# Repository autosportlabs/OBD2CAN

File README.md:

OBD2CAN
=======

OBD2CAN allows cars with pre-CAN OBDII enabled ECUs (1996-2007) to emulate a CAN-OBDII interface.

Target
======

OBD2CAN was originally designed as an enhancement to the RaceCapture and RaceCapture/Pro line of hardware, but could theoretically be used with any device that can only communicate with CAN-OBDII enabled ECUs.

Principal of Operation
======================

The operation of OBD2CAN is straightforward:

CAN-OBDII requests are received by OBD2CAN and are forwarded on to the legacy-OBDII interface, using
a STN1110 processor and interface circuitry. 

Legacy-OBDII PID responses are received from the STN1110, and transformed back into the equivalent CAN-OBDII response.

Firmware
========
The firmware is targeted for the STM32F072, and uses ChibiOS as a RTOS. 

Compiling
=========
Compiling requires arm-none-eabi gcc version 4.7.4 20130913

From the firmware directory issue:

> make clean

> make

Flashing
========
* ST bootloader

The firmware image can be flashed using the ST bootloader using the USART1 header after activating BOOT mode. On the OBD2CAN hardware the BOOT jumper pads is adjacent to the USART1 header. The USART header can be connected to a common FTDI 3.3v USB-USART cable (TTL-232R-3V3).

* JTAG SWD

An openocd script is provided to flash the STM32 via SWD, using a ST-LINK/V2

Operation
=========

CAN PID requests are received per OBDII SAE specifications and are translated 1:1 to STN1110 PID requests for the target ECU. 
* 500KBPS
* 11 bit

Protocol is set for automatic detection. 

Diagnostic and command/control CAN messages
===========================================

Control Message
===============
The control message allows some control over the OBD2CAN module's settings

CAN ID: 62344

* Byte 0: Sub command.
 * always 0x01

* Byte 1: Debug level on UART header
 * 0: no logging
 * 1: info level logging
 * 2: trace level logging

* Byte 2: Reset STN1110
 * 0: do not reset
 * 1: perform a hard reset

* Byte 3: Set OBDII protocol
Affects AT SP command, see ELM327 manual. If different than the current setting, triggers a reset of the STN1110
 * 0: auto detect (power up default)
 * 1: J1850 PWM
 * 2: J1850 VPW
 * 3: ISO 9141-2
 * 4: ISO 14230-4

Diagnostic
==========
The OBD2CAN will broadcast a diagnostic message at 1Hz with the following information:

CAN ID: 62345

* Byte 0: Detected protocol
 * 0: auto detect (still detecting)
 * 1: J1850 PWM
 * 2: J1850 VPW
 * 3: ISO 9141-2
 * 4: ISO 14230-4

* Byte 1: Last error code
 * 0: STN1110_ERROR_NONE,
 * 1: STN1110_ERROR_STOPPED,
 * 2: STN1110_ERROR_NO_DATA,
 * 3: STN1110_ERROR_BUS_INIT

* Byte 2-3: STN1110 request/reply latency, in ms. 
 * Little Endian

* Byte 4: reserved

* Byte 5: firmware major version

* Byte 6: firmware minor version

* Byte 7: firmware patch version

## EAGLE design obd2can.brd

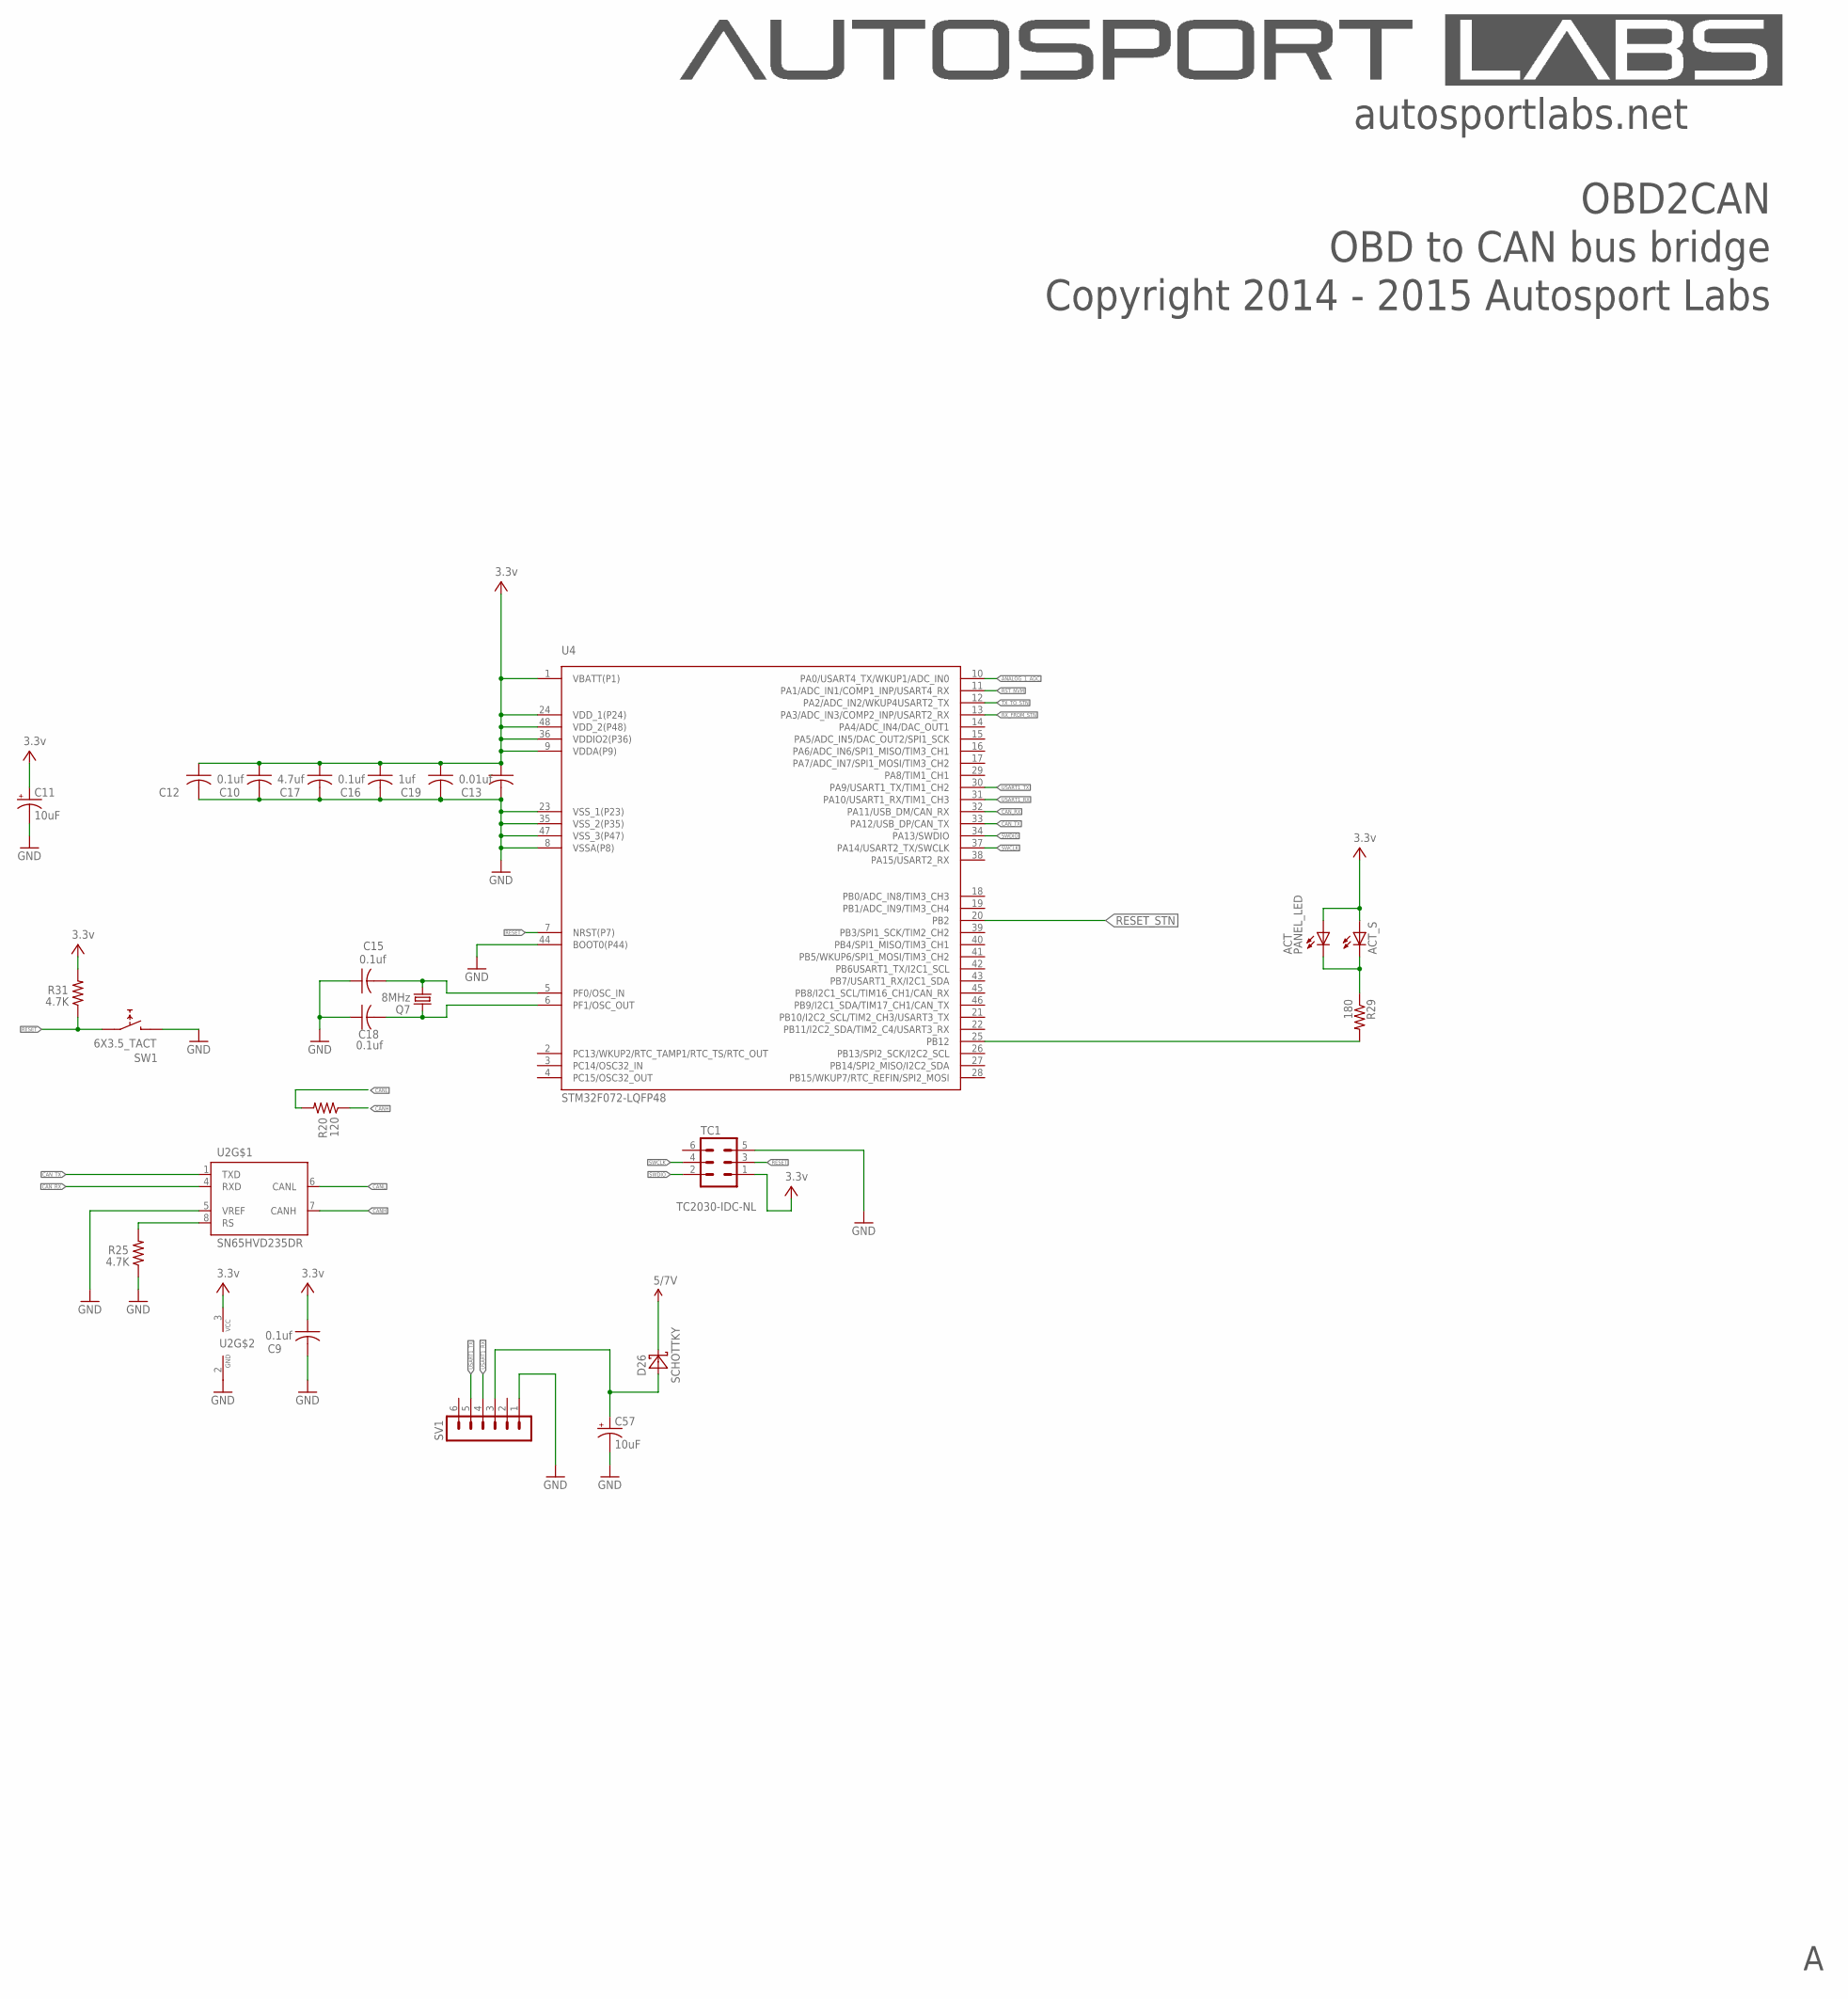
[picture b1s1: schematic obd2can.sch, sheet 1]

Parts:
ACT: PANEL_LED; RIGHTANGLE_CML_5323F5
ACT_S: LEDCHIPLED_0603; CHIPLED_0603
C9, C10, C15, C16, C18: 0.1uf; C0603K
C11, C57: 10uF; SMC_A
C12, C17: 4.7uf; C0603K
C13: 0.01uf; C0603K
C19: 1uf; C0603K
D26: SCHOTTKY; SMA
Q7: 8MHz; CRYSTAL-SMD-5X3
R20: 120; R0603
R25, R31: 4.7K; R0603
R29: 180; 0402-RES
SV1: MA06-1
SW1: 6X3.5_TACT; TACT_6X3.5
TC1: TC2030-IDC-NL
U2: SN65HVD235DR; SO08
U4: STM32F072-LQFP48; LQFP48

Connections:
ANALOG_1_ADC: U4.10 (PA0/USART4_TX/WKUP1/ADC_IN0)
CANH: R20.1, U2.7 (CANH); also elsewhere on the board
CANL: R20.2, U2.6 (CANL); also elsewhere on the board
CAN_RX: U2.4 (RXD), U4.32 (PA11/USB_DM/CAN_RX)
CAN_TX: U2.1 (TXD), U4.33 (PA12/USB_DP/CAN_TX)
GND: C9.2, C10.2, C11.-, C12.2, C13.2, C15.1, C16.2, C17.2, C18.1, C19.2, C57.-, R25.1, SV1.1, SW1.P$2 (2), TC1.5, U2.2 (GND), U2.5 (VREF), U4.8 (VSSA(P8)), U4.23 (VSS_1(P23)), U4.35 (VSS_2(P35)), U4.44 (BOOT0(P44)), U4.47 (VSS_3(P47)); also elsewhere on the board
GND1: ACT.C, ACT_S.C, R29.1
unnamed: R29.2, U4.25 (PB12)
unnamed: R25.2, U2.8 (RS)
unnamed: C18.2, Q7.3 (2), U4.6 (PF1/OSC_OUT)
unnamed: C15.2, Q7.1, U4.5 (PF0/OSC_IN)
RESET: R31.1, SW1.P$1 (1), TC1.3, U4.7 (NRST(P7))
RESET_STN: U4.20 (PB2); also elsewhere on the board
RST_NVM: U4.11 (PA1/ADC_IN1/COMP1_INP/USART4_RX); also elsewhere on the board
RX_FROM_STN: U4.13 (PA3/ADC_IN3/COMP2_INP/USART2_RX); also elsewhere on the board
SWCLK: TC1.4, U4.37 (PA14/USART2_TX/SWCLK)
SWDIO: TC1.2, U4.34 (PA13/SWDIO)
TX_TO_STN: U4.12 (PA2/ADC_IN2/WKUP4USART2_TX); also elsewhere on the board
USART1_RX: SV1.4, U4.31 (PA10/USART1_RX/TIM1_CH3)
USART1_TX: SV1.5, U4.30 (PA9/USART1_TX/TIM1_CH2)
V+: ACT.A, ACT_S.A, C9.1, C10.1, C11.+, C12.1, C13.1, C16.1, C17.1, C19.1, R31.2, TC1.1, U2.3 (VCC), U4.1 (VBATT(P1)), U4.9 (VDDA(P9)), U4.24 (VDD_1(P24)), U4.36 (VDDIO2(P36)), U4.48 (VDD_2(P48)); also elsewhere on the board
VBUS: C57.+, D26.A, SV1.3
VCC: D26.C; also elsewhere on the board

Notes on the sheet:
Copyright 2014 - 2015 Autosport Labs
OBD2CAN
autosportlabs.net
OBD to CAN bus bridge

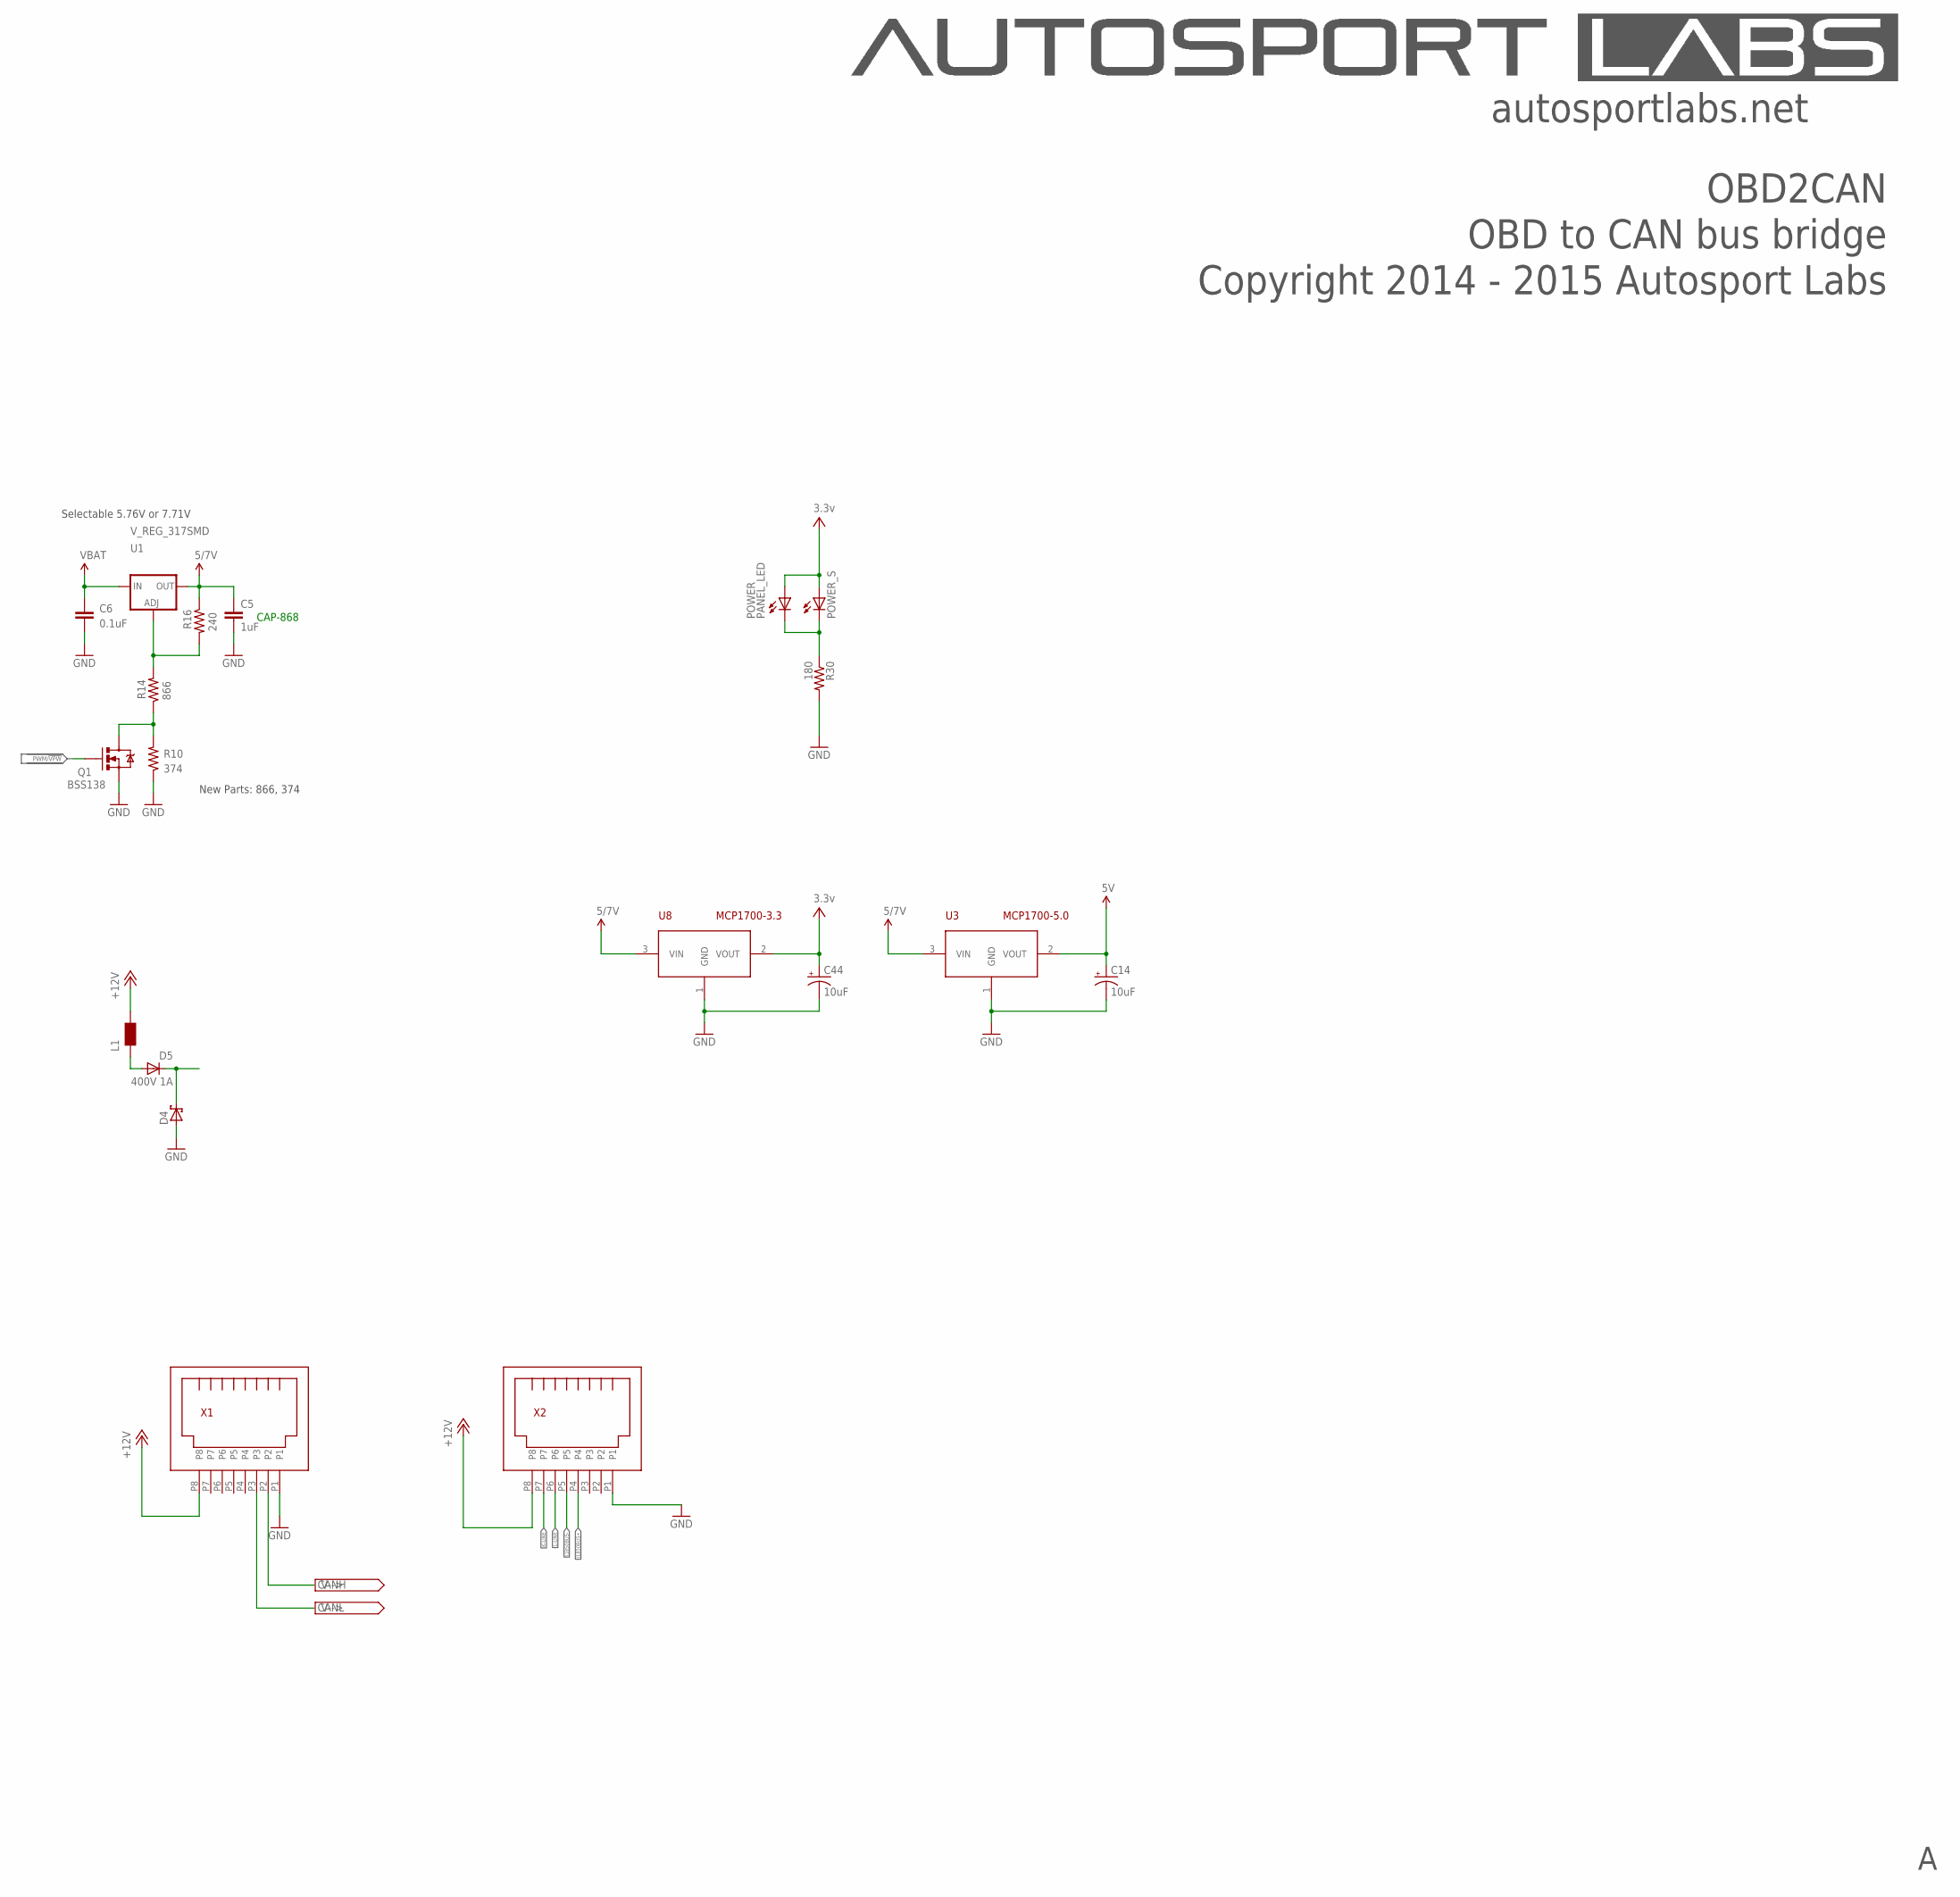
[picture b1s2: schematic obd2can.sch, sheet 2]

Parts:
C5: 1uF; 0402-CAP
C6: 0.1uF; 0402-CAP
C14, C44: 10uF; SMC_A
D4: SCHOTTKY-DIODESMC; SMC
D5: 400V 1A; SMA
L1: WE-CBF_1812; 1812
POWER: PANEL_LED; RIGHTANGLE_CML_5323F5
POWER_S: LEDCHIPLED_0603; CHIPLED_0603
Q1: BSS138; SOT23-3
R10: 374; 0402-RES
R14: 866; 0402-RES
R16: 240; 0402-RES
R30: 180; 0402-RES
U1: V_REG_317SMD; SOT223
U3: MCP1700-5.0; SOT-23
U8: MCP1700-3.3; SOT-23
X1, X2: RJ45_RIGHT_ANGLEMOLEX_95001-2881; RJ45_RIGHT_ANGLE_MOLEX_95001-2881

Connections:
5V: C14.+, U3.2 (VOUT); also elsewhere on the board
+12V: L1.2, X1.P8, X2.P8; also elsewhere on the board
CANH: X1.P2; also elsewhere on the board
CANL: X1.P3; also elsewhere on the board
GND: C5.2, C6.2, C14.-, C44.-, D4.A, Q1.2 (S), R10.1, R30.2, U3.1 (GND), U8.1 (GND), X1.P1, X2.P1; also elsewhere on the board
GND2: POWER.C, POWER_S.C, R30.1
J1850BUS+: X2.P4; also elsewhere on the board
J1850BUS-: X2.P5; also elsewhere on the board
K-LINE: X2.P7; also elsewhere on the board
L-LINE: X2.P6; also elsewhere on the board
unnamed: R14.2, R16.2, U1.1 (ADJ)
unnamed: Q1.3 (D), R10.2, R14.1
unnamed: D5.A, L1.1
PWM/!VPW: Q1.1 (G); also elsewhere on the board
SAFE12V: C6.1, D4.C, D5.C, U1.3 (IN); also elsewhere on the board
V+: C44.+, POWER.A, POWER_S.A, U8.2 (VOUT); also elsewhere on the board
VCC: C5.1, R16.1, U1.2 (OUT), U3.3 (VIN), U8.3 (VIN); also elsewhere on the board

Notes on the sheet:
Copyright 2014 - 2015 Autosport Labs
OBD2CAN
autosportlabs.net
OBD to CAN bus bridge
Selectable 5.76V or 7.71V
New Parts: 866, 374
CAP-868

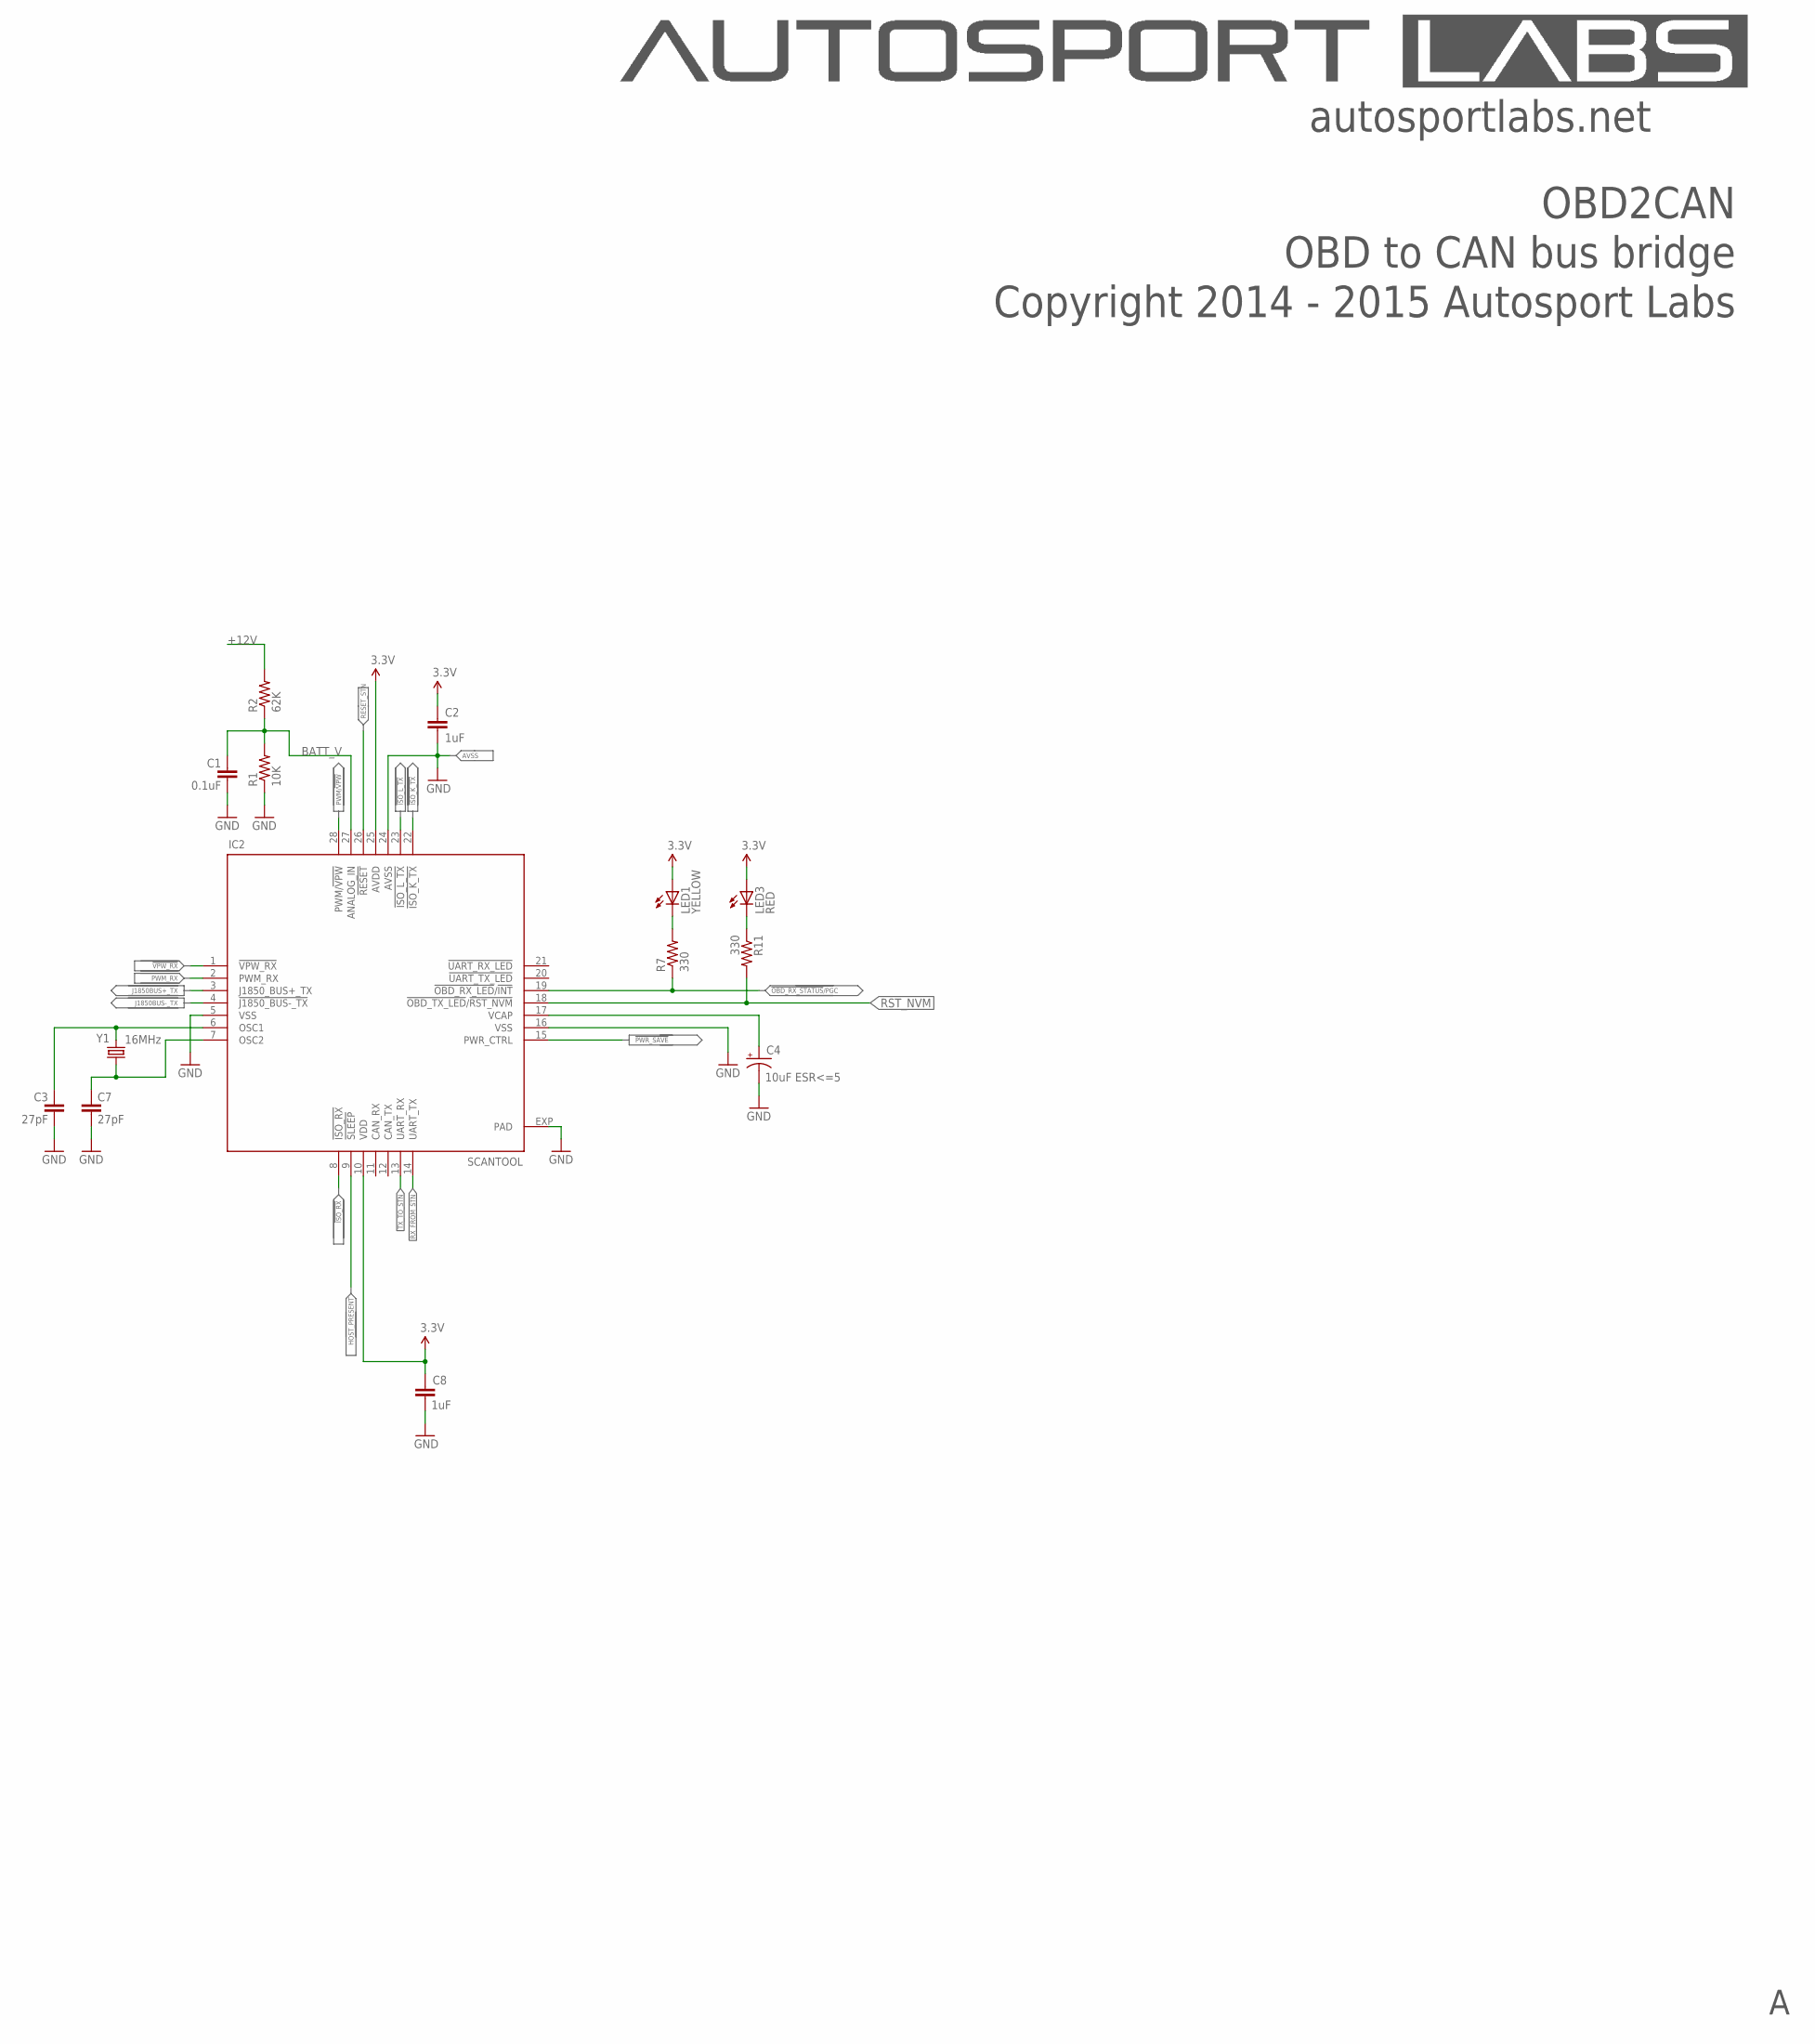
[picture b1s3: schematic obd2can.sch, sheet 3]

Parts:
C1: 0.1uF; 0402-CAP
C2, C8: 1uF; 0402-CAP
C3, C7: 27pF; 0402-CAP
C4: 10uF ESR<=5; EIA3216
IC2: SCANTOOL; _STN_SCANTOOL_QFN-28-S
LED1: YELLOW; LED-0603
LED3: RED; LED-0603
R1: 10K; 0402-RES
R2: 62K; 0402-RES
R7, R11: 330; 0402-RES
Y1: 16MHz; CRYSTAL-SMD-5X3

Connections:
!ISO_K_TX: IC2.22 (!ISO_K_TX); also elsewhere on the board
!ISO_L_TX: IC2.23 (!ISO_L_TX); also elsewhere on the board
!ISO_RX: IC2.8 (!ISO_RX); also elsewhere on the board
!OBD_RX_STATUS!/PGC: IC2.19 (!OBD_RX_LED!/!INT), R7.1
!PWR_SAVE: IC2.15 (PWR_CTRL)
!VPW_RX: IC2.1 (!VPW_RX); also elsewhere on the board
+12V: R2.2; also elsewhere on the board
BATT_V: C1.1, IC2.27 (ANALOG_IN), R1.2, R2.1
GND: C1.2, C2.2, C3.2, C4.C (-), C7.2, C8.2, IC2.5 (VSS), IC2.16 (VSS), IC2.24 (AVSS), IC2.EXP (PAD), R1.1; also elsewhere on the board
HOST_PRESENT: IC2.9 (!SLEEP)
J1850BUS+_TX: IC2.3 (J1850_BUS+_TX); also elsewhere on the board
J1850BUS-_TX: IC2.4 (!J1850_BUS-_TX); also elsewhere on the board
unnamed: C4.A (+), IC2.17 (VCAP)
unnamed: LED1.C, R7.2
unnamed: LED3.C, R11.1
OSC1: C3.1, IC2.6 (OSC1), Y1.3 (2)
OSC2: C7.1, IC2.7 (OSC2), Y1.1
PWM/!VPW: IC2.28 (PWM/!VPW); also elsewhere on the board
PWM_RX: IC2.2 (PWM_RX); also elsewhere on the board
RESET_STN: IC2.26 (!RESET); also elsewhere on the board
RST_NVM: IC2.18 (!OBD_TX_LED!/!RST_NVM), R11.2; also elsewhere on the board
RX_FROM_STN: IC2.14 (UART_TX); also elsewhere on the board
TX_TO_STN: IC2.13 (UART_RX); also elsewhere on the board
V+: C2.1, C8.1, IC2.10 (VDD), IC2.25 (AVDD), LED1.A, LED3.A; also elsewhere on the board

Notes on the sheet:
AVSS
Copyright 2014 - 2015 Autosport Labs
OBD2CAN
autosportlabs.net
OBD to CAN bus bridge

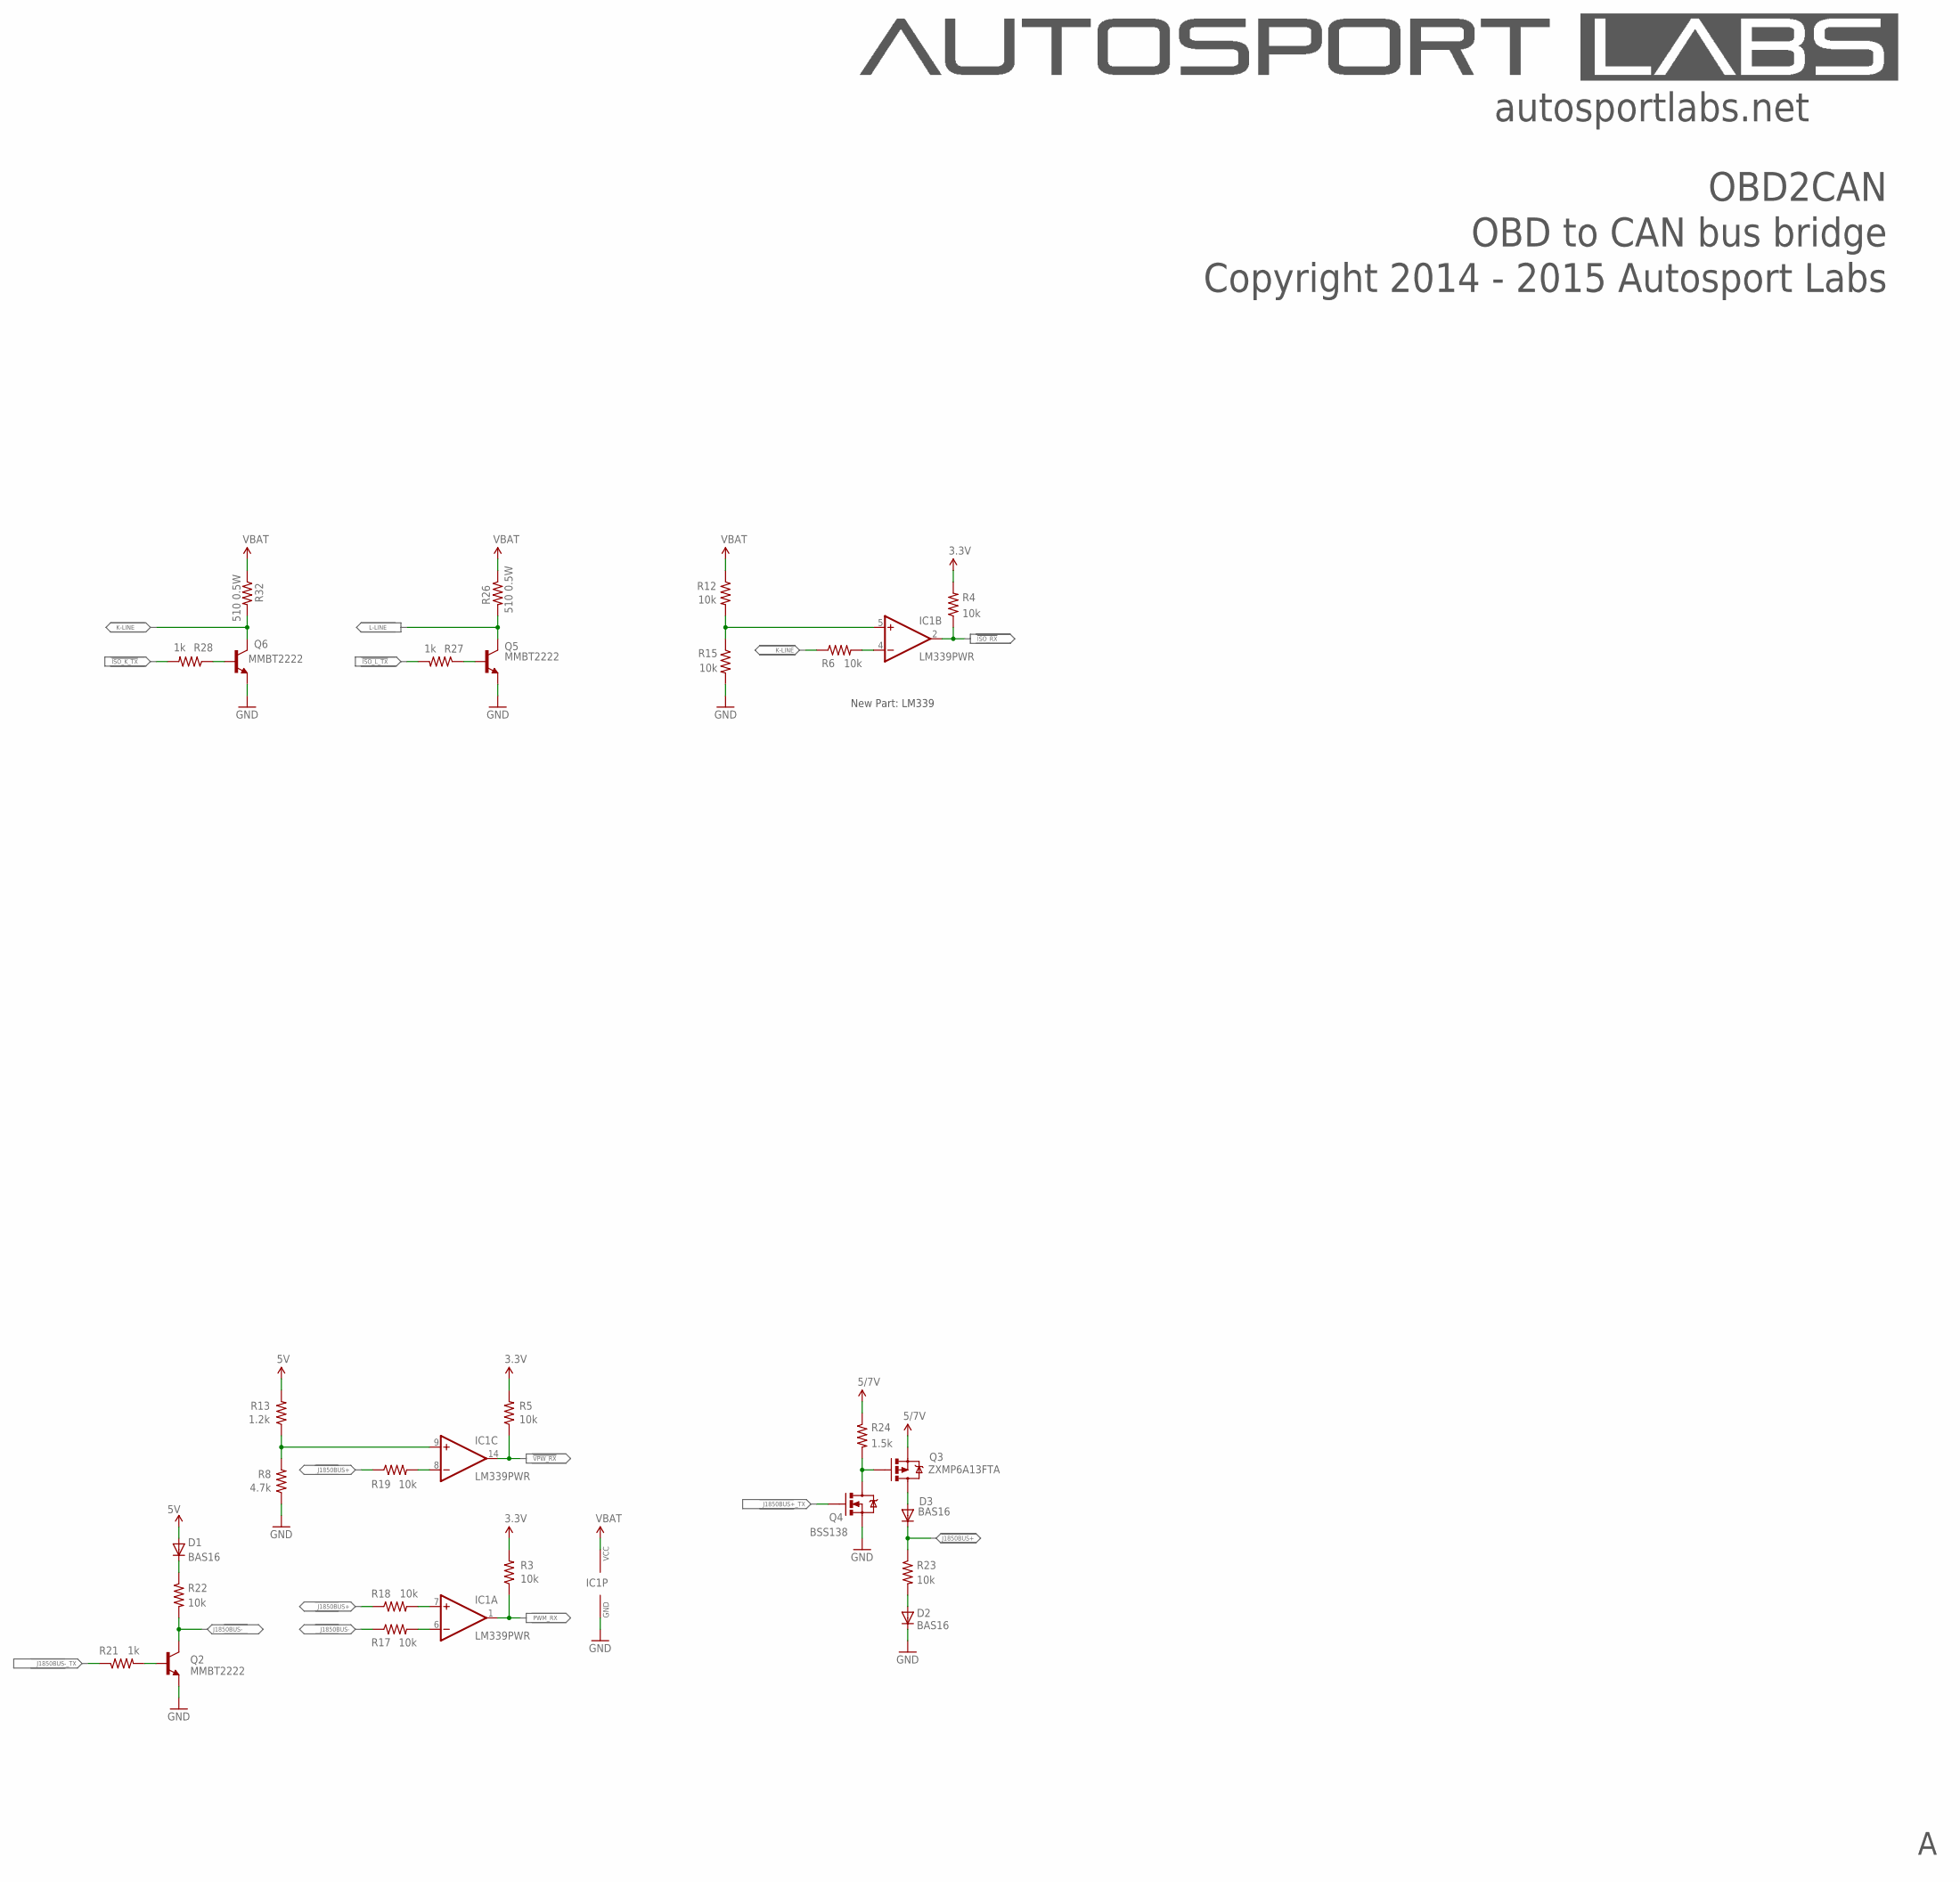
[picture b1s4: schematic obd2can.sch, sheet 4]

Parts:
D1, D2, D3: BAS16; SOD-323
IC1: LM339PWR; TSSOP-14
Q2, Q5, Q6: MMBT2222; SOT23-3
Q3: ZXMP6A13FTA; SOT23
Q4: BSS138; SOT23-3
R3, R4, R5, R6, R12, R15, R17, R18, R19, R22, R23: 10k; 0402-RES
R8: 4.7k; 0402-RES
R13: 1.2k; 0402-RES
R21, R27, R28: 1k; 0402-RES
R24: 1.5k; 0402-RES
R26, R32: 510 0.5W; 2010

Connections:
5V: D1.2 (A), R13.2; also elsewhere on the board
!ISO_K_TX: R28.2; also elsewhere on the board
!ISO_L_TX: R27.2; also elsewhere on the board
!ISO_RX: IC1.2 (OUT), R4.1; also elsewhere on the board
!VPW_RX: IC1.14 (OUT), R5.1; also elsewhere on the board
GND: D2.1 (C), IC1.12 (GND), Q2.2 (E), Q4.2 (S), Q5.2 (E), Q6.2 (E), R8.1, R15.2; also elsewhere on the board
J1850BUS+: D3.1 (C), R18.1, R19.1, R23.1; also elsewhere on the board
J1850BUS+_TX: Q4.1 (G); also elsewhere on the board
J1850BUS-: Q2.3 (C), R17.1, R22.2; also elsewhere on the board
J1850BUS-_TX: R21.1; also elsewhere on the board
K-LINE: Q6.3 (C), R6.1, R32.2; also elsewhere on the board
L-LINE: Q5.3 (C), R26.2; also elsewhere on the board
unnamed: IC1.7 (+IN), R18.2
unnamed: IC1.6 (-IN), R17.2
unnamed: Q6.1 (B), R28.1
unnamed: Q5.1 (B), R27.1
unnamed: IC1.5 (+IN), R12.2, R15.1
unnamed: IC1.8 (-IN), R19.2
unnamed: D3.2 (A), Q3.3 (D)
unnamed: IC1.9 (+IN), R8.2, R13.1
unnamed: IC1.4 (-IN), R6.2
unnamed: D1.1 (C), R22.1
unnamed: Q3.1 (G), Q4.3 (D), R24.2
unnamed: D2.2 (A), R23.2
unnamed: Q2.1 (B), R21.2
PWM_RX: IC1.1 (OUT), R3.1; also elsewhere on the board
SAFE12V: IC1.3 (VCC), R12.1, R26.1, R32.1; also elsewhere on the board
V+: R3.2, R4.2, R5.2; also elsewhere on the board
VCC: Q3.2 (S), R24.1; also elsewhere on the board

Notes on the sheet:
Copyright 2014 - 2015 Autosport Labs
OBD2CAN
autosportlabs.net
OBD to CAN bus bridge
New Part: LM339
